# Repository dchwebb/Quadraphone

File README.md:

# Quadraphone

Quadraphone
--------

Quadraphone is a four voice polyphonic analog Voltage Controlled Oscillator for use within a Eurorack Modular Synthesiser. Polyphonic signal interconnections are made via RJ-45 cables (ie Ethernet cables).

Quadraphone features a switchable output of square, triangle and saw waves. Pulse Width Modulation (PWM) is available for the square wave, polyphonically via an RJ-45 input or across all voices via a 3.5mm jack. A potentiometer sets the default pulse width across all voices.

Polyphonic synch is available and a switch allows selection of hard, soft or off settings. Exponentional FM is available on an Rj-45 connection and vibrato (linear FM) is available via a 3.5mm jack with potentiometer attenuation.

A volt per octave input is available on an RJ-45 connector. Pins 1-4 carry the control voltage input and pins 5-8 carry the output signal (also available on an RJ-45) for easy module interconnection. Coarse and Fine tune potentiometers affect all voices.

Technical
---------

Each Quadraphone voice is based around the [Sound Semiconductor SSI2131 Fatkeys VCO](https://www.soundsemiconductor.com/).

Each VCO outputs three voices (pulse, triangle and saw) which are switched via Nexperia 74LV4066PW analog switches. 74LV4066PW ICs are also used to switch incoming synch signals between the hard, soft and off selections.

Each voice has trimmers to control base frequency, exponential scaling and high frequency tracking.

Construction is a sandwich of three PCBs with a component board, a controls board and a panel. PCBs designed in Kicad v6.

[Components schematic](https://raw.githubusercontent.com/dchwebb/Quadraphone/master/Quadraphone_Components.pdf)

[Controls schematic](https://raw.githubusercontent.com/dchwebb/Quadraphone/master/Quadraphone_Controls.pdf)

In addition the the Eurorack +/-12V rails (which have polarity protection and filtering) a 5v rail is supplied using an AMS1117-5.0 LDO. A 2.5v rail is generated with an LM4040DBZ-2.5 and buffered with an MCP6002 opamp and a -5v reference is generated with an LM4040DBZ-5.0.

+12V current draw: 44mA
-12V current draw: 34mA

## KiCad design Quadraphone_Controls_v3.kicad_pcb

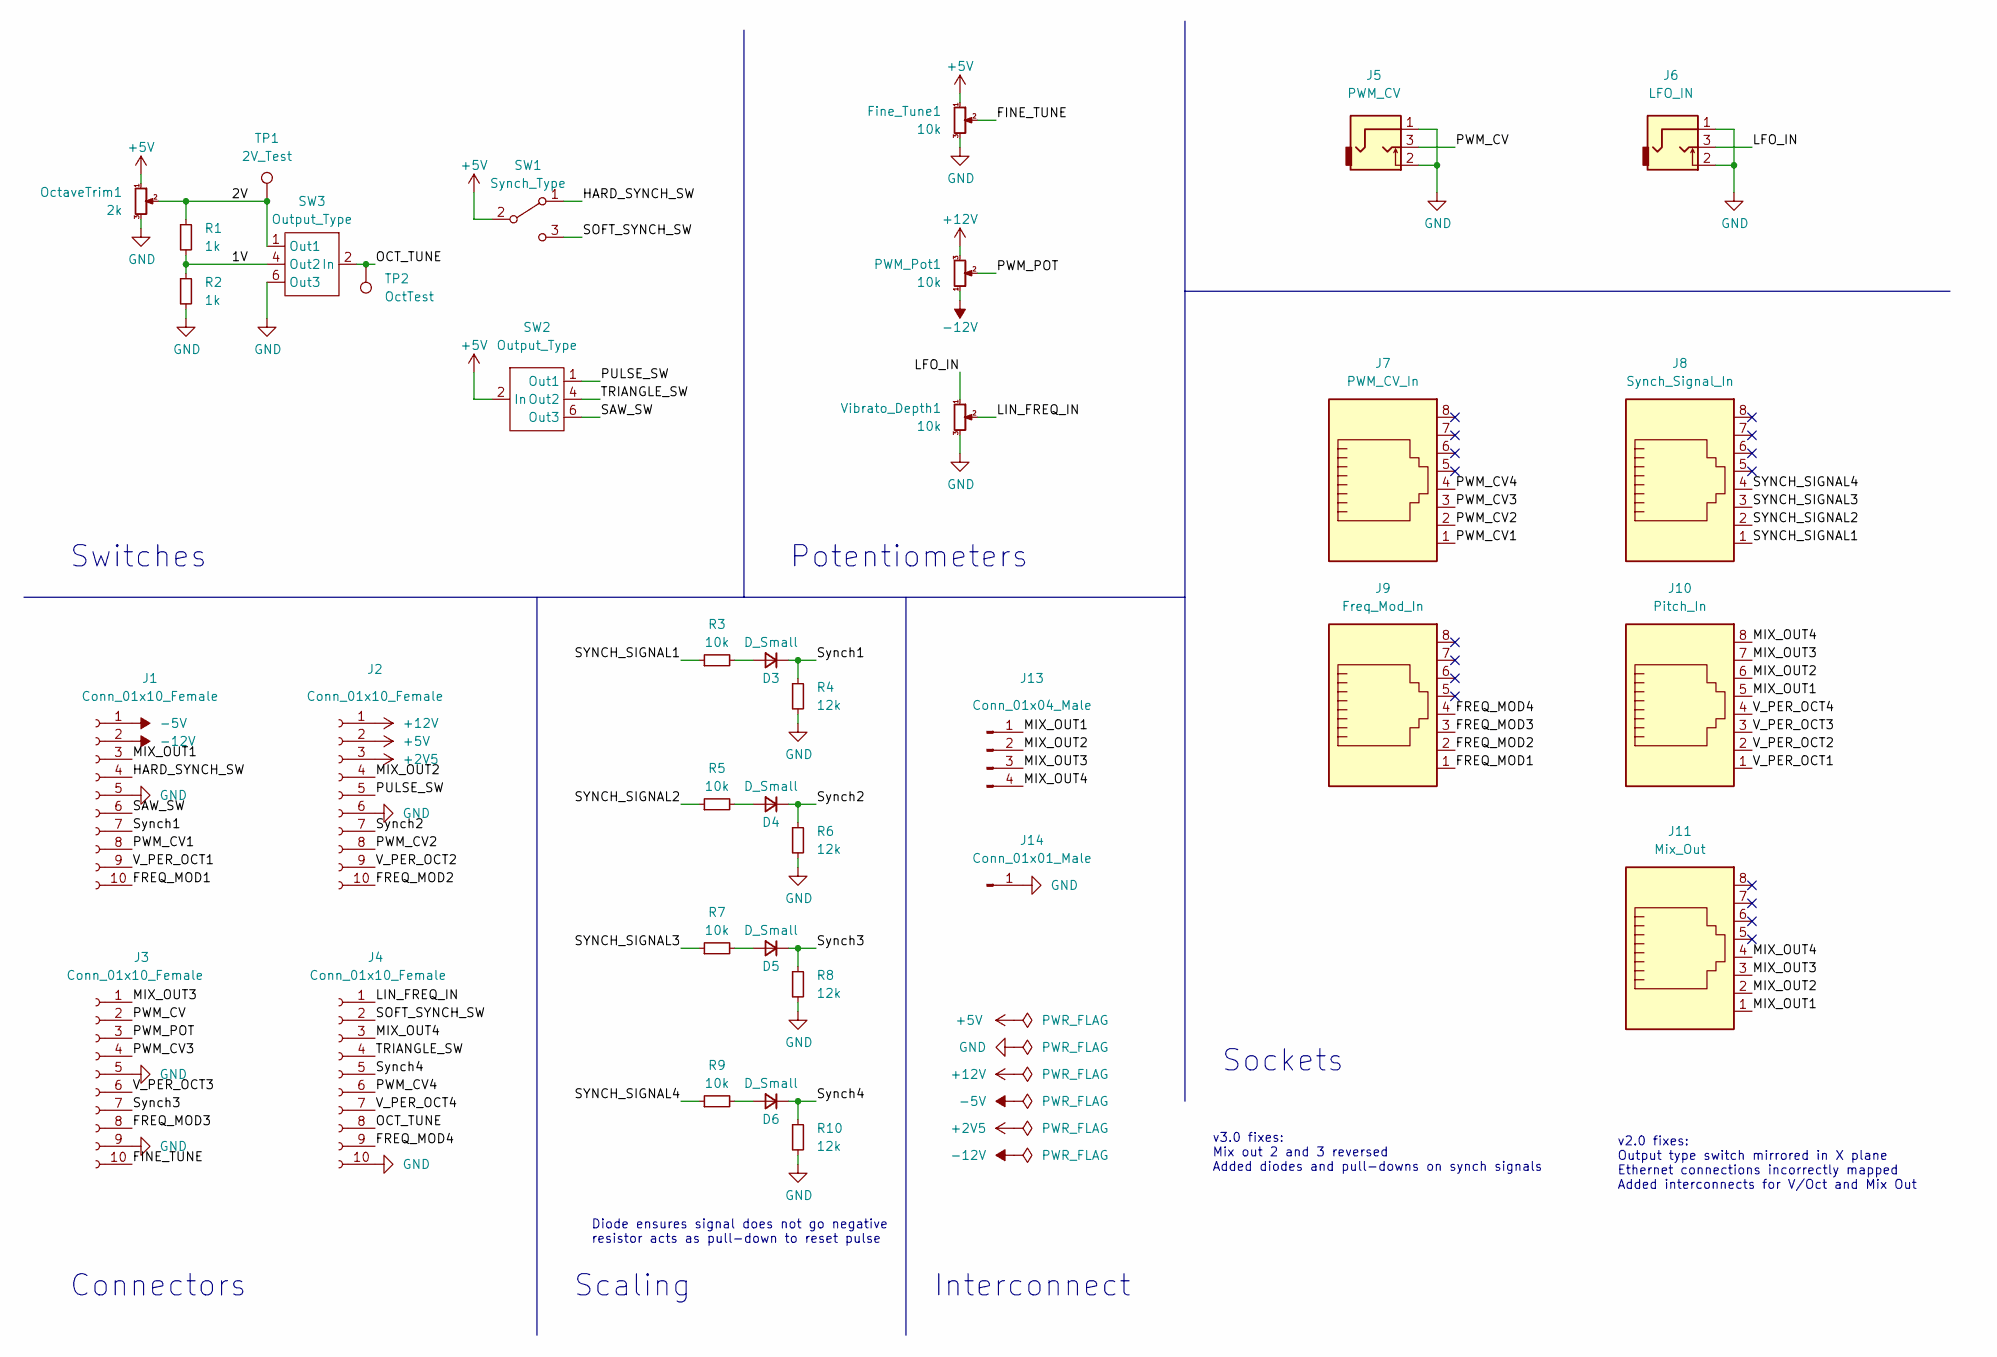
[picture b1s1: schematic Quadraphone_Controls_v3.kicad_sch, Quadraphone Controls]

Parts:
D3, D4, D5, D6: D_Small; D_0603_1608Metric_Pad1.05x0.95mm_HandSolder
Fine_Tune1: 10k; Alpha_9mm_Potentiometer_Aligned
J1, J2, J3, J4: Conn_01x10_Female; PinSocket_1x10_P2.54mm_Vertical
J5: PWM_CV; THONKICONN_hole
J6: LFO_IN; THONKICONN_hole
J7: PWM_CV_In; RJ45_Molex_42878-8506
J8: Synch_Signal_In; RJ45_Molex_42878-8506
J9: Freq_Mod_In; RJ45_Molex_42878-8506
J10: Pitch_In; RJ45_Molex_42878-8506
J11: Mix_Out; RJ45_Molex_42878-8506
J13: Conn_01x04_Male; PinHeader_1x04_P2.54mm_Vertical
J14: Conn_01x01_Male; PinHeader_1x01_P2.54mm_Vertical
OctaveTrim1: 2k; Potentiometer_Bourns_3266W_Vertical
PWM_Pot1: 10k; Alpha_9mm_Potentiometer_Aligned
R1, R2: 1k; R_0805_2012Metric
R3, R5, R7, R9: 10k; R_0805_2012Metric
R4, R6, R8, R10: 12k; R_0805_2012Metric
SW1: Synch_Type; SPDTSubMiniature
SW2, SW3: Output_Type; 100DP6T1B1M2QE_ON_ON_ON
TP1: 2V_Test; 1mm_Test_Point
TP2: OctTest; 1mm_Test_Point
Vibrato_Depth1: 10k; Alpha_9mm_Potentiometer_Aligned

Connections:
+2V5: J2.3
+5V: Fine_Tune1.1, J2.2, OctaveTrim1.1, SW1.2 (B), SW2.2 (In)
+12V: J2.1, PWM_Pot1.3
-5V: J1.1
-12V: J1.2, PWM_Pot1.1
/1V: R1.2, R2.1, SW3.4 (Out2)
/2V: OctaveTrim1.2, R1.1, SW3.1 (Out1), TP1.1
/FINE_TUNE: Fine_Tune1.2, J3.10
/FREQ_MOD1: J1.10, J9.1
/FREQ_MOD2: J2.10, J9.2
/FREQ_MOD3: J3.8, J9.3
/FREQ_MOD4: J4.9, J9.4
/HARD_SYNCH_SW: J1.4, SW1.1 (A)
/LFO_IN: J6.3, Vibrato_Depth1.1
/LIN_FREQ_IN: J4.1, Vibrato_Depth1.2
/MIX_OUT1: J1.3, J10.5, J11.1, J13.1
/MIX_OUT2: J2.4, J10.6, J11.2, J13.2
/MIX_OUT3: J3.1, J10.7, J11.3, J13.3
/MIX_OUT4: J4.3, J10.8, J11.4, J13.4
/OCT_TUNE: J4.8, SW3.2 (In), TP2.1
/PULSE_SW: J2.5, SW2.1 (Out1)
/PWM_CV: J3.2, J5.3
/PWM_CV1: J1.8, J7.1
/PWM_CV2: J2.8, J7.2
/PWM_CV3: J3.4, J7.3
/PWM_CV4: J4.6, J7.4
/PWM_POT: J3.3, PWM_Pot1.2
/SAW_SW: J1.6, SW2.6 (Out3)
/SOFT_SYNCH_SW: J4.2, SW1.3 (C)
/SYNCH_SIGNAL1: J8.1, R3.1
/SYNCH_SIGNAL2: J8.2, R5.1
/SYNCH_SIGNAL3: J8.3, R7.1
/SYNCH_SIGNAL4: J8.4, R9.1
/Synch1: D3.1 (K), J1.7, R4.1
/Synch2: D4.1 (K), J2.7, R6.1
/Synch3: D5.1 (K), J3.7, R8.1
/Synch4: D6.1 (K), J4.5, R10.1
/TRIANGLE_SW: J4.4, SW2.4 (Out2)
/V_PER_OCT1: J1.9, J10.1
/V_PER_OCT2: J2.9, J10.2
/V_PER_OCT3: J3.6, J10.3
/V_PER_OCT4: J4.7, J10.4
GND: Fine_Tune1.3, J1.5, J2.6, J3.5, J3.9, J4.10, J5.1, J5.2, J6.1, J6.2, J14.1, OctaveTrim1.3, R2.2, R4.2, R6.2, R8.2, R10.2, SW3.6 (Out3), Vibrato_Depth1.3
unnamed: D3.2 (A), R3.2
unnamed: D4.2 (A), R5.2
unnamed: D5.2 (A), R7.2
unnamed: D6.2 (A), R9.2
unnamed: SW2.3 (Pin3), SW2.5 (Pin5)
unnamed: SW3.3 (Pin3), SW3.5 (Pin5)

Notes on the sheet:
Connectors
Diode ensures signal does not go negative resistor acts as pull-down to reset pulse
Scaling
Potentiometers
v2.0 fixes: Output type switch mirrored in X plane Ethernet connections incorrectly mapped Added interconnects for V/Oct and Mix Out
v3.0 fixes: Mix out 2 and 3 reversed Added diodes and pull-downs on synch signals
Sockets
Switches
Interconnect

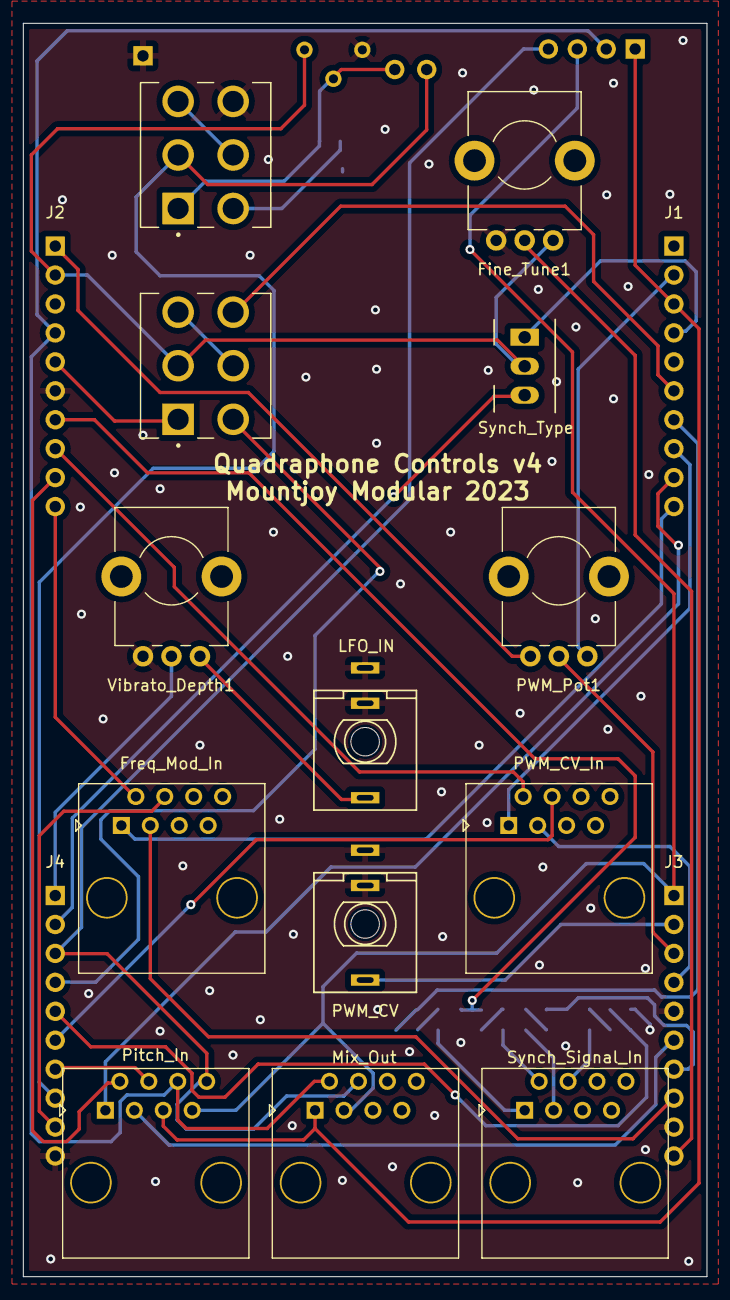
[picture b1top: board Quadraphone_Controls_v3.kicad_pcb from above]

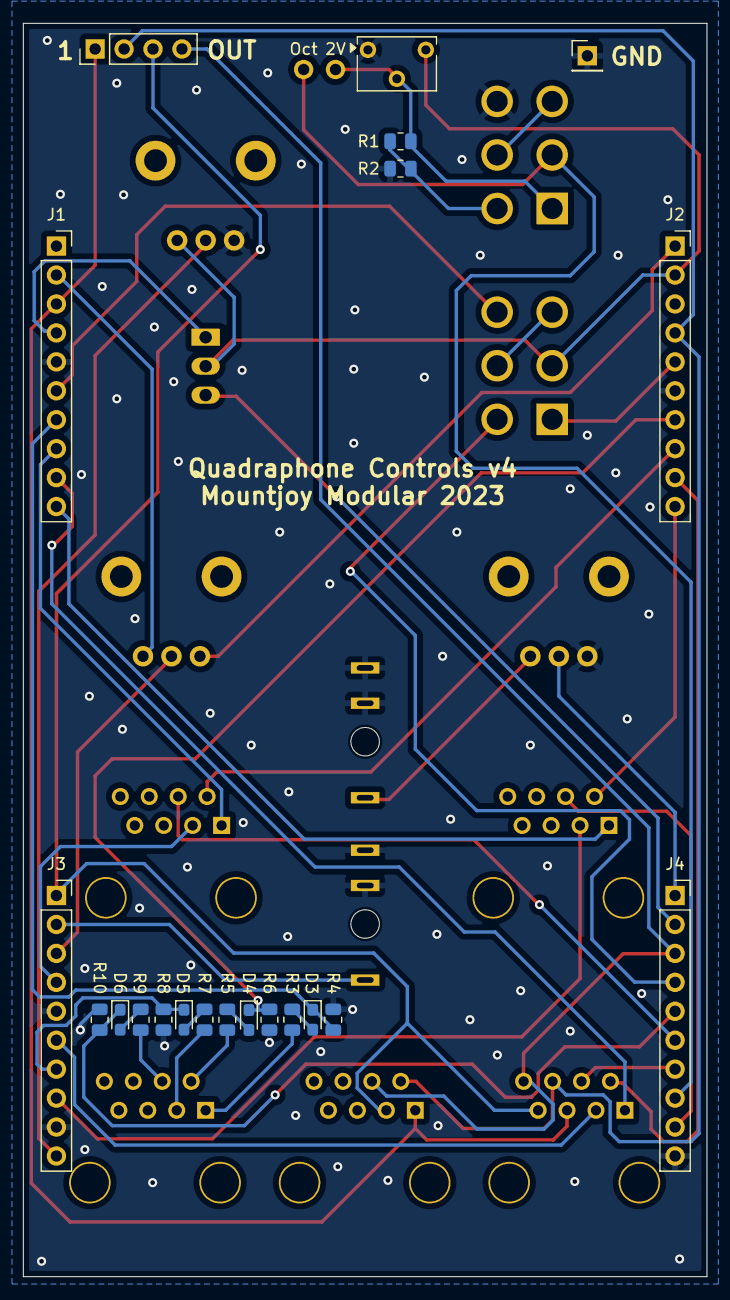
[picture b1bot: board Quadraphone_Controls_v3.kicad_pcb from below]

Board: 2 copper layers, 60.0 x 110.0 mm, 36 parts (21 on the bottom side), 47 nets.

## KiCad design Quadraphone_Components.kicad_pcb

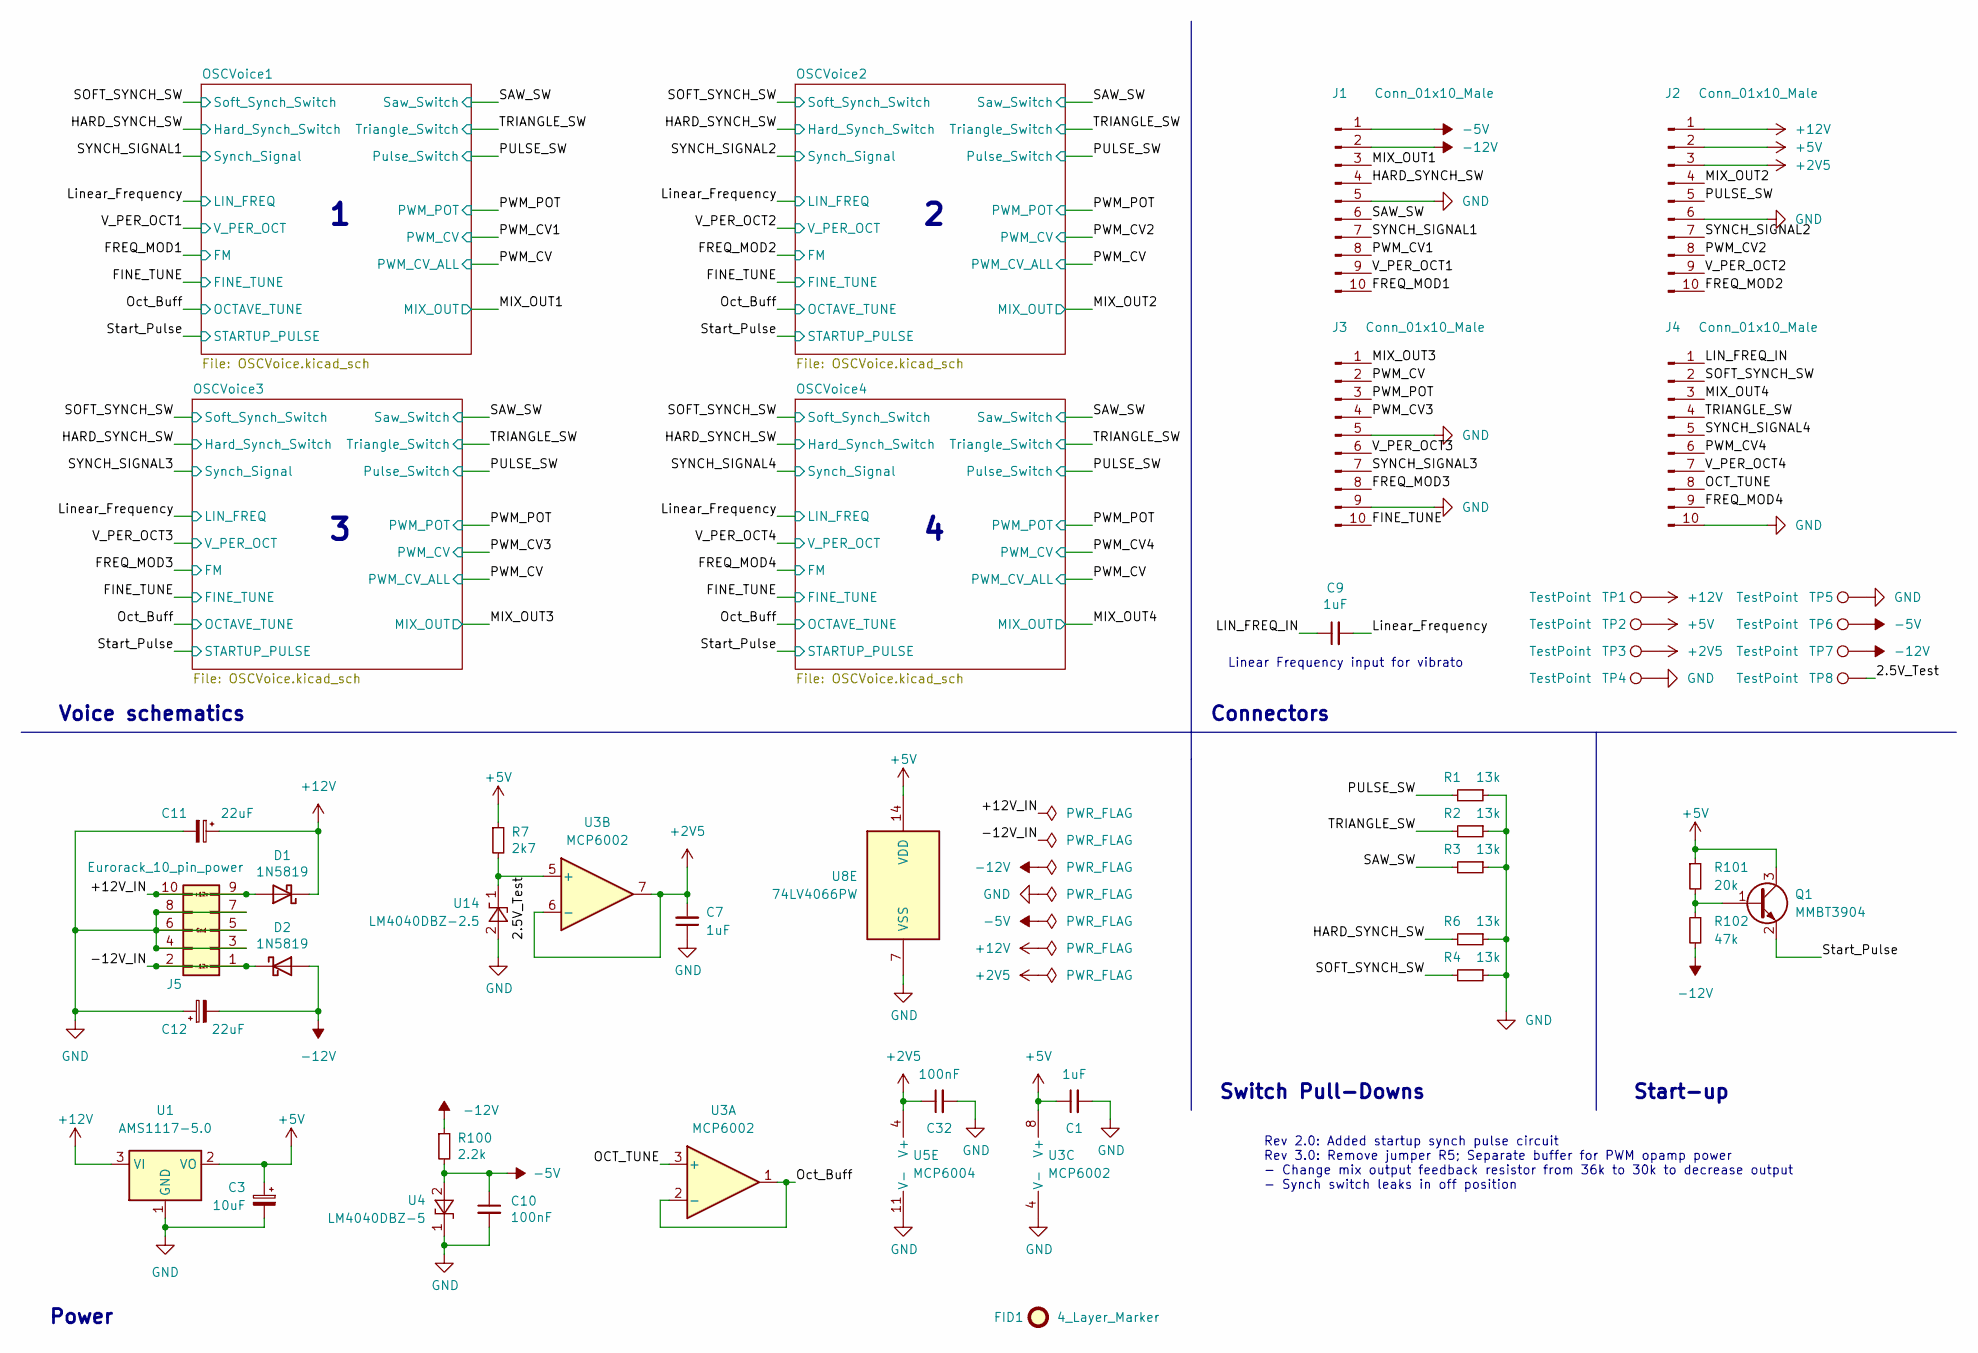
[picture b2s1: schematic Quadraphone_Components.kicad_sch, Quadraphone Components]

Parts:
C1, C7, C9: 1uF; C_0603_1608Metric_Pad1.08x0.95mm_HandSolder
C3: 10uF; CP_Elec_4x5.7
C10, C32: 100nF; C_0603_1608Metric_Pad1.08x0.95mm_HandSolder
C11, C12: 22uF; CP_Elec_4x5.8
D1, D2: 1N5819; D_SOD-123
FID1: 4_Layer_Marker; 4_Layer_Markers
J1, J2, J3, J4: Conn_01x10_Male; PinHeader_1x10_P2.54mm_Vertical
J5: Eurorack_10_pin_power; Eurorack_10_pin_header
Q1: MMBT3904; SOT-23
R1, R2, R3, R4, R6: 13k; R_0603_1608Metric
R7: 2k7; R_0603_1608Metric
R100: 2.2k; R_0603_1608Metric
R101: 20k; R_0603_1608Metric
R102: 47k; R_0603_1608Metric
TP1, TP2, TP3, TP4, TP5, TP6, TP7, TP8: TestPoint; 1.3mm_Test_Point
U1: AMS1117-5.0; SOT-223-3_TabPin2
U3: MCP6002; SOIC-8_3.9x4.9mm_P1.27mm
U4: LM4040DBZ-5; SOT-23
U5: MCP6004; SOIC-14_3.9x8.7mm_P1.27mm
U8: 74LV4066PW; TSSOP-14_4.4x5mm_P0.65mm
U14: LM4040DBZ-2.5; SOT-23

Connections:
+2V5: C7.2, C32.1, J2.3, TP3.1, U3.6 (-), U3.7, U5.4 (V+); also elsewhere on the board
+5V: C1.1, C3.1, J2.2, Q1.3 (C), R7.1, R101.1, TP2.1, U1.2 (VO), U3.8 (V+), U8.14 (VDD); also elsewhere on the board
+12V: C11.1, D1.1 (K), J2.1, TP1.1, U1.3 (VI); also elsewhere on the board
-5V: C10.1, J1.1, R100.2, TP6.1, U4.2 (A); also elsewhere on the board
-12V: C12.2, D2.2 (A), J1.2, R100.1, R102.2, TP7.1; also elsewhere on the board
/2.5V_Test: R7.2, TP8.1, U3.5 (+), U14.1 (K)
/+12V_IN: D1.2 (A), J5.9, J5.10
/-12V_IN: D2.1 (K), J5.1, J5.2
/FINE_TUNE: J3.10; also elsewhere on the board
/FREQ_MOD1: J1.10; also elsewhere on the board
/FREQ_MOD2: J2.10; also elsewhere on the board
/FREQ_MOD3: J3.8; also elsewhere on the board
/FREQ_MOD4: J4.9; also elsewhere on the board
/HARD_SYNCH_SW: J1.4, R6.2; also elsewhere on the board
/LIN_FREQ_IN: C9.1, J4.1
/Linear_Frequency: C9.2; also elsewhere on the board
/MIX_OUT1: J1.3; also elsewhere on the board
/MIX_OUT2: J2.4; also elsewhere on the board
/MIX_OUT3: J3.1; also elsewhere on the board
/MIX_OUT4: J4.3; also elsewhere on the board
/OCT_TUNE: J4.8, U3.3 (+)
/OSCVoice1/PWM_Control: U5.7; also elsewhere on the board
/OSCVoice1/PWM_Opamp_Mix: U5.6 (-); also elsewhere on the board
/OSCVoice1/Soft_Synch: U8.9; also elsewhere on the board
/OSCVoice2/PWM_Control: U5.1; also elsewhere on the board
/OSCVoice2/PWM_Opamp_Mix: U5.2 (-); also elsewhere on the board
/OSCVoice2/Soft_Synch: U8.3; also elsewhere on the board
/OSCVoice4/PWM_Control: U5.14; also elsewhere on the board
/OSCVoice4/PWM_Opamp_Mix: U5.13 (-); also elsewhere on the board
/OSCVoice4/Soft_Synch: U8.2; also elsewhere on the board
/Oct_Buff: U3.1, U3.2 (-); also elsewhere on the board
/PULSE_SW: J2.5, R1.2; also elsewhere on the board
/PWM_CV: J3.2; also elsewhere on the board
/PWM_CV1: J1.8; also elsewhere on the board
/PWM_CV2: J2.8; also elsewhere on the board
/PWM_CV3: J3.4; also elsewhere on the board
/PWM_CV4: J4.6; also elsewhere on the board
/PWM_POT: J3.3; also elsewhere on the board
/SAW_SW: J1.6, R3.2; also elsewhere on the board
/SOFT_SYNCH_SW: J4.2, R4.2, U8.5, U8.6, U8.13; also elsewhere on the board
/SYNCH_SIGNAL1: J1.7, U8.8; also elsewhere on the board
/SYNCH_SIGNAL2: J2.7, U8.4; also elsewhere on the board
/SYNCH_SIGNAL3: J3.7; also elsewhere on the board
/SYNCH_SIGNAL4: J4.5, U8.1; also elsewhere on the board
/Start_Pulse: Q1.2 (E); also elsewhere on the board
/TRIANGLE_SW: J4.4, R2.2; also elsewhere on the board
/V_PER_OCT1: J1.9; also elsewhere on the board
/V_PER_OCT2: J2.9; also elsewhere on the board
/V_PER_OCT3: J3.6; also elsewhere on the board
/V_PER_OCT4: J4.7; also elsewhere on the board
GND: C1.2, C3.2, C7.1, C10.2, C11.2, C12.1, C32.2, J1.5, J2.6, J3.5, J3.9, J4.10, J5.3, J5.4, J5.5, J5.6, J5.7, J5.8, R1.1, R2.1, R3.1, R4.1, R6.1, TP4.1, TP5.1, U1.1 (GND), U3.4 (V-), U4.1 (K), U5.3 (+), U5.5 (+), U5.11 (V-), U5.12 (+), U8.7 (VSS), U14.2 (A); also elsewhere on the board
unnamed: Q1.1 (B), R101.2, R102.1

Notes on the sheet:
Rev 2.0: Added startup synch pulse circuit Rev 3.0: Remove jumper R5; Separate buffer for PWM opamp power - Change mix output feedback resistor from 36k to 30k to decrease output - Synch switch leaks in off position
Linear Frequency input for vibrato
Start-up
Switch Pull-Downs
Connectors
Power
Voice schematics

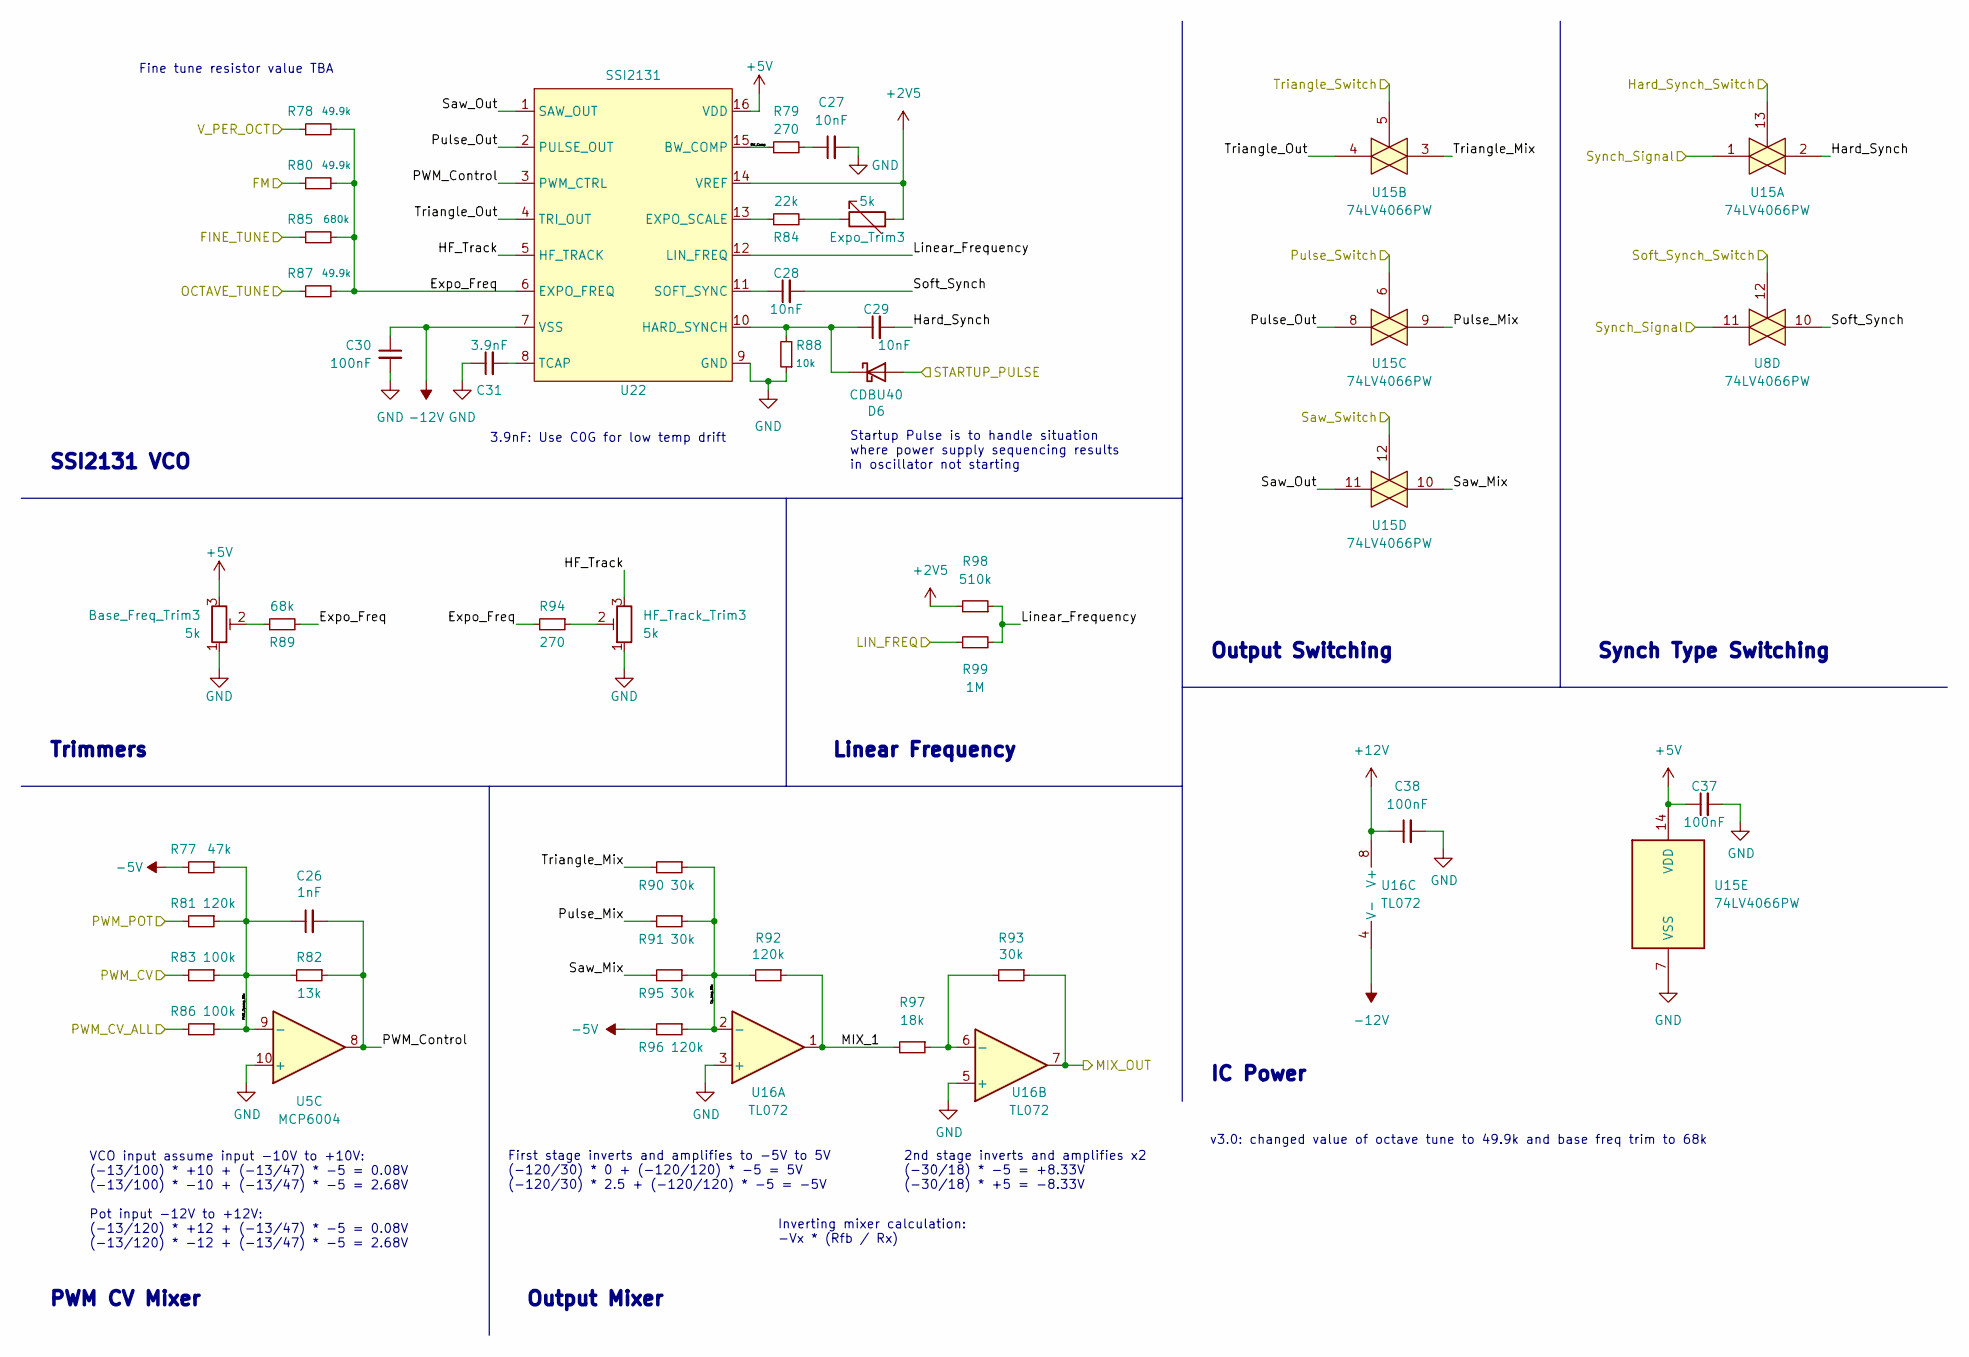
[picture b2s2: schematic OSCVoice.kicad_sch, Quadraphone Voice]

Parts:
Base_Freq_Trim3: 5k; Potentiometer_Bourns_3266W_Vertical
C26: 1nF; C_0603_1608Metric_Pad1.08x0.95mm_HandSolder
C27, C28, C29: 10nF; C_0603_1608Metric_Pad1.08x0.95mm_HandSolder
C30, C37, C38: 100nF; C_0603_1608Metric_Pad1.08x0.95mm_HandSolder
C31: 3.9nF; C_0603_1608Metric_Pad1.08x0.95mm_HandSolder
D6: CDBU40; D_0603_1608Metric
Expo_Trim3: 5k; Potentiometer_Bourns_3266W_Vertical
HF_Track_Trim3: 5k; Potentiometer_Bourns_3266W_Vertical
R77: 47k; R_0603_1608Metric
R78, R80, R87: 49.9k; R_0603_1608Metric
R79, R94: 270; R_0603_1608Metric
R81, R92, R96: 120k; R_0603_1608Metric
R82: 13k; R_0603_1608Metric
R83, R86: 100k; R_0603_1608Metric
R84: 22k; R_0603_1608Metric
R85: 680k; R_0603_1608Metric
R88: 10k; R_0603_1608Metric
R89: 68k; R_0603_1608Metric
R90, R91, R93, R95: 30k; R_0603_1608Metric
R97: 18k; R_0603_1608Metric
R98: 510k; R_0603_1608Metric
R99: 1M; R_0603_1608Metric
U5: MCP6004; SOIC-14_3.9x8.7mm_P1.27mm
U8, U15: 74LV4066PW; TSSOP-14_4.4x5mm_P0.65mm
U16: TL072; SOIC-8_3.9x4.9mm_P1.27mm
U22: SSI2131; SOIC-16_3.9x9.9mm_P1.27mm

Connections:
+2V5: Expo_Trim3.2, R98.2, U22.14 (VREF); also elsewhere on the board
+5V: Base_Freq_Trim3.3, C37.1, U15.14 (VDD), U22.16 (VDD); also elsewhere on the board
+12V: C38.1, U16.8 (V+); also elsewhere on the board
-5V: R77.2, R96.2; also elsewhere on the board
-12V: C30.1, U16.4 (V-), U22.7 (VSS); also elsewhere on the board
/FINE_TUNE: R85.1; also elsewhere on the board
/FREQ_MOD3: R80.1; also elsewhere on the board
/HARD_SYNCH_SW: U15.13; also elsewhere on the board
/Linear_Frequency: R99.1; also elsewhere on the board
/MIX_OUT3: R93.1, U16.7; also elsewhere on the board
/OSCVoice1/PWM_Control: U5.7; also elsewhere on the board
/OSCVoice1/PWM_Opamp_Mix: U5.6 (-); also elsewhere on the board
/OSCVoice1/Soft_Synch: U8.9; also elsewhere on the board
/OSCVoice2/PWM_Control: U5.1; also elsewhere on the board
/OSCVoice2/PWM_Opamp_Mix: U5.2 (-); also elsewhere on the board
/OSCVoice2/Soft_Synch: U8.3; also elsewhere on the board
/OSCVoice3/BW_Comp: R79.1, U22.15 (BW_COMP)
/OSCVoice3/Expo_Freq: R78.2, R80.2, R85.2, R87.2, R89.2, R94.2, U22.6 (EXPO_FREQ)
/OSCVoice3/HF_Track: HF_Track_Trim3.3, U22.5 (HF_TRACK)
/OSCVoice3/Hard_Synch: C29.2, U15.2
/OSCVoice3/Linear_Frequency: R98.1, R99.2, U22.12 (LIN_FREQ)
/OSCVoice3/MIX_1: R92.1, R97.2, U16.1
/OSCVoice3/Op_Amp_Mix: R90.1, R91.1, R92.2, R95.1, R96.1, U16.2 (-)
/OSCVoice3/PWM_Control: C26.2, R82.1, U5.8, U22.3 (PWM_CTRL)
/OSCVoice3/PWM_Opamp_Mix: C26.1, R77.1, R81.1, R82.2, R83.1, R86.1, U5.9 (-)
/OSCVoice3/Pulse_Mix: R91.2, U15.9
/OSCVoice3/Pulse_Out: U15.8, U22.2 (PULSE_OUT)
/OSCVoice3/Saw_Mix: R95.2, U15.10
/OSCVoice3/Saw_Out: U15.11, U22.1 (SAW_OUT)
/OSCVoice3/Soft_Synch: C28.2, U8.10
/OSCVoice3/Triangle_Mix: R90.2, U15.3
/OSCVoice3/Triangle_Out: U15.4, U22.4 (TRI_OUT)
/OSCVoice4/PWM_Control: U5.14; also elsewhere on the board
/OSCVoice4/PWM_Opamp_Mix: U5.13 (-); also elsewhere on the board
/OSCVoice4/Soft_Synch: U8.2; also elsewhere on the board
/Oct_Buff: R87.1; also elsewhere on the board
/PULSE_SW: U15.6; also elsewhere on the board
/PWM_CV: R86.2; also elsewhere on the board
/PWM_CV3: R83.2; also elsewhere on the board
/PWM_POT: R81.2; also elsewhere on the board
/SAW_SW: U15.12; also elsewhere on the board
/SOFT_SYNCH_SW: U8.5, U8.6, U8.12, U8.13; also elsewhere on the board
/SYNCH_SIGNAL1: U8.8; also elsewhere on the board
/SYNCH_SIGNAL2: U8.4; also elsewhere on the board
/SYNCH_SIGNAL3: U8.11, U15.1; also elsewhere on the board
/SYNCH_SIGNAL4: U8.1; also elsewhere on the board
/Start_Pulse: D6.2 (A); also elsewhere on the board
/TRIANGLE_SW: U15.5; also elsewhere on the board
/V_PER_OCT3: R78.1; also elsewhere on the board
GND: Base_Freq_Trim3.1, C27.2, C30.2, C31.1, C37.2, C38.2, HF_Track_Trim3.1, R88.1, U5.3 (+), U5.5 (+), U5.10 (+), U5.12 (+), U15.7 (VSS), U16.3 (+), U16.5 (+), U22.9 (GND); also elsewhere on the board
unnamed: Base_Freq_Trim3.2, R89.1
unnamed: C27.1, R79.2
unnamed: C29.1, D6.1 (K), R88.2, U22.10 (HARD_SYNCH)
unnamed: Expo_Trim3.1, R84.2
unnamed: HF_Track_Trim3.2, R94.1
unnamed: R93.2, R97.1, U16.6 (-)
unnamed: R84.1, U22.13 (EXPO_SCALE)
unnamed: C28.1, U22.11 (SOFT_SYNC)
unnamed: C31.2, U22.8 (TCAP)

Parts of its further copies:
Base_Freq_Trim1, Base_Freq_Trim2, Base_Freq_Trim4: 5k; Potentiometer_Bourns_3266W_Vertical
C4, C5, C6, C15, C16, C17, C21, C22, C23: 10nF; C_0603_1608Metric_Pad1.08x0.95mm_HandSolder
C8, C19, C25: 3.9nF; C_0603_1608Metric_Pad1.08x0.95mm_HandSolder
C13, C14, C20: 1nF; C_0603_1608Metric_Pad1.08x0.95mm_HandSolder
C18, C24, C33, C34, C35, C36, C39, C40, C41: 100nF; C_0603_1608Metric_Pad1.08x0.95mm_HandSolder
D3, D4, D5: CDBU40; D_0603_1608Metric
Expo_Trim1, Expo_Trim2, Expo_Trim4: 5k; Potentiometer_Bourns_3266W_Vertical
HF_Track_Trim1, HF_Track_Trim2, HF_Track_Trim4: 5k; Potentiometer_Bourns_3266W_Vertical
R8, R38, R61: 22k; R_0603_1608Metric
R9, R42, R65: 10k; R_0603_1608Metric
R10, R16, R33, R48, R56, R71: 270; R_0603_1608Metric
R11, R31, R54: 47k; R_0603_1608Metric
R12, R21, R28, R35, R46, R50, R58, R69, R73: 120k; R_0603_1608Metric
R13, R15, R25, R40, R60, R63: 100k; R_0603_1608Metric
R14, R36, R59: 13k; R_0603_1608Metric
R17, R39, R62: 680k; R_0603_1608Metric
R18, R22, R32, R34, R37, R41, R55, R57, R64: 49.9k; R_0603_1608Metric
R19, R20, R26, R27, R44, R45, R47, R49, R67, R68, R70, R72: 30k; R_0603_1608Metric
R23, R43, R66: 68k; R_0603_1608Metric
R24, R52, R75: 510k; R_0603_1608Metric
R29, R51, R74: 18k; R_0603_1608Metric
R30, R53, R76: 1M; R_0603_1608Metric
U6, U7, U11: 74LV4066PW; TSSOP-14_4.4x5mm_P0.65mm
U9, U12, U17: SSI2131; SOIC-16_3.9x9.9mm_P1.27mm
U10, U13, U18: TL072; SOIC-8_3.9x4.9mm_P1.27mm

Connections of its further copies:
+2V5: Expo_Trim1.2, Expo_Trim2.2, Expo_Trim4.2, R24.2, R52.2, R75.2, U9.14 (VREF), U12.14 (VREF), U17.14 (VREF); also elsewhere on the board
+5V: Base_Freq_Trim1.3, Base_Freq_Trim2.3, Base_Freq_Trim4.3, C33.1, C35.1, C39.1, U6.14 (VDD), U7.14 (VDD), U9.16 (VDD), U11.14 (VDD), U12.16 (VDD), U17.16 (VDD); also elsewhere on the board
+12V: C34.1, C36.1, C40.1, U10.8 (V+), U13.8 (V+), U18.8 (V+); also elsewhere on the board
-5V: R11.2, R28.2, R31.2, R50.2, R54.2, R73.2; also elsewhere on the board
-12V: C18.1, C24.1, C41.1, U9.7 (VSS), U10.4 (V-), U12.7 (VSS), U13.4 (V-), U17.7 (VSS), U18.4 (V-); also elsewhere on the board
/FINE_TUNE: R17.1, R39.1, R62.1; also elsewhere on the board
/FREQ_MOD1: R18.1; also elsewhere on the board
/FREQ_MOD2: R34.1; also elsewhere on the board
/FREQ_MOD4: R57.1; also elsewhere on the board
/HARD_SYNCH_SW: U6.13, U7.13, U11.13; also elsewhere on the board
/Linear_Frequency: R30.1, R53.1, R76.1; also elsewhere on the board
/MIX_OUT1: R26.1, U10.7; also elsewhere on the board
/MIX_OUT2: R47.1, U13.7; also elsewhere on the board
/MIX_OUT4: R70.1, U18.7; also elsewhere on the board
/OSCVoice1/BW_Comp: R10.1, U9.15 (BW_COMP)
/OSCVoice1/Expo_Freq: R16.2, R17.2, R18.2, R22.2, R23.2, R37.2, U9.6 (EXPO_FREQ)
/OSCVoice1/HF_Track: HF_Track_Trim1.3, U9.5 (HF_TRACK)
/OSCVoice1/Hard_Synch: C6.2, U6.2
/OSCVoice1/Linear_Frequency: R24.1, R30.2, U9.12 (LIN_FREQ)
/OSCVoice1/MIX_1: R21.1, R29.2, U10.1
/OSCVoice1/Op_Amp_Mix: R19.1, R20.1, R21.2, R27.1, R28.1, U10.2 (-)
/OSCVoice1/PWM_Control: C13.2, R14.1, U9.3 (PWM_CTRL); also elsewhere on the board
/OSCVoice1/PWM_Opamp_Mix: C13.1, R11.1, R12.1, R14.2, R15.1, R25.1; also elsewhere on the board
/OSCVoice1/Pulse_Mix: R20.2, U6.9
/OSCVoice1/Pulse_Out: U6.8, U9.2 (PULSE_OUT)
/OSCVoice1/Saw_Mix: R27.2, U6.10
/OSCVoice1/Saw_Out: U6.11, U9.1 (SAW_OUT)
/OSCVoice1/Soft_Synch: C5.2; also elsewhere on the board
/OSCVoice1/Triangle_Mix: R19.2, U6.3
/OSCVoice1/Triangle_Out: U6.4, U9.4 (TRI_OUT)
/OSCVoice2/BW_Comp: R33.1, U12.15 (BW_COMP)
/OSCVoice2/Expo_Freq: R32.2, R34.2, R39.2, R41.2, R43.2, R48.2, U12.6 (EXPO_FREQ)
/OSCVoice2/HF_Track: HF_Track_Trim2.3, U12.5 (HF_TRACK)
/OSCVoice2/Hard_Synch: C17.2, U7.2
/OSCVoice2/Linear_Frequency: R52.1, R53.2, U12.12 (LIN_FREQ)
/OSCVoice2/MIX_1: R46.1, R51.2, U13.1
/OSCVoice2/Op_Amp_Mix: R44.1, R45.1, R46.2, R49.1, R50.1, U13.2 (-)
/OSCVoice2/PWM_Control: C14.2, R36.1, U12.3 (PWM_CTRL); also elsewhere on the board
/OSCVoice2/PWM_Opamp_Mix: C14.1, R31.1, R35.1, R36.2, R40.1, R60.1; also elsewhere on the board
/OSCVoice2/Pulse_Mix: R45.2, U7.9
/OSCVoice2/Pulse_Out: U7.8, U12.2 (PULSE_OUT)
/OSCVoice2/Saw_Mix: R49.2, U7.10
/OSCVoice2/Saw_Out: U7.11, U12.1 (SAW_OUT)
/OSCVoice2/Soft_Synch: C16.2; also elsewhere on the board
/OSCVoice2/Triangle_Mix: R44.2, U7.3
/OSCVoice2/Triangle_Out: U7.4, U12.4 (TRI_OUT)
/OSCVoice4/BW_Comp: R56.1, U17.15 (BW_COMP)
/OSCVoice4/Expo_Freq: R55.2, R57.2, R62.2, R64.2, R66.2, R71.2, U17.6 (EXPO_FREQ)
/OSCVoice4/HF_Track: HF_Track_Trim4.3, U17.5 (HF_TRACK)
/OSCVoice4/Hard_Synch: C23.2, U11.2
/OSCVoice4/Linear_Frequency: R75.1, R76.2, U17.12 (LIN_FREQ)
/OSCVoice4/MIX_1: R69.1, R74.2, U18.1
/OSCVoice4/Op_Amp_Mix: R67.1, R68.1, R69.2, R72.1, R73.1, U18.2 (-)
/OSCVoice4/PWM_Control: C20.2, R59.1, U17.3 (PWM_CTRL); also elsewhere on the board
/OSCVoice4/PWM_Opamp_Mix: C20.1, R13.1, R54.1, R58.1, R59.2, R63.1; also elsewhere on the board
/OSCVoice4/Pulse_Mix: R68.2, U11.9
/OSCVoice4/Pulse_Out: U11.8, U17.2 (PULSE_OUT)
/OSCVoice4/Saw_Mix: R72.2, U11.10
/OSCVoice4/Saw_Out: U11.11, U17.1 (SAW_OUT)
/OSCVoice4/Soft_Synch: C22.2; also elsewhere on the board
/OSCVoice4/Triangle_Mix: R67.2, U11.3
/OSCVoice4/Triangle_Out: U11.4, U17.4 (TRI_OUT)
/Oct_Buff: R22.1, R41.1, R64.1; also elsewhere on the board
/PULSE_SW: U6.6, U7.6, U11.6; also elsewhere on the board
/PWM_CV: R15.2, R40.2, R63.2; also elsewhere on the board
/PWM_CV1: R25.2; also elsewhere on the board
/PWM_CV2: R60.2; also elsewhere on the board
/PWM_CV4: R13.2; also elsewhere on the board
/PWM_POT: R12.2, R35.2, R58.2; also elsewhere on the board
/SAW_SW: U6.12, U7.12, U11.12; also elsewhere on the board
/SYNCH_SIGNAL1: U6.1; also elsewhere on the board
/SYNCH_SIGNAL2: U7.1; also elsewhere on the board
/SYNCH_SIGNAL4: U11.1; also elsewhere on the board
/Start_Pulse: D3.2 (A), D4.2 (A), D5.2 (A); also elsewhere on the board
/TRIANGLE_SW: U6.5, U7.5, U11.5; also elsewhere on the board
/V_PER_OCT1: R37.1; also elsewhere on the board
/V_PER_OCT2: R32.1; also elsewhere on the board
/V_PER_OCT4: R55.1; also elsewhere on the board
GND: Base_Freq_Trim1.1, Base_Freq_Trim2.1, Base_Freq_Trim4.1, C4.2, C8.1, C15.2, C18.2, C19.1, C21.2, C24.2, C25.1, C33.2, C34.2, C35.2, C36.2, C39.2, C40.2, C41.2, HF_Track_Trim1.1, HF_Track_Trim2.1, HF_Track_Trim4.1, R9.1, R42.1, R65.1, U6.7 (VSS), U7.7 (VSS), U9.9 (GND), U10.3 (+), U10.5 (+), U11.7 (VSS), U12.9 (GND), U13.3 (+), U13.5 (+), U17.9 (GND), U18.3 (+), U18.5 (+); also elsewhere on the board
unnamed: Base_Freq_Trim1.2, R23.1
unnamed: Base_Freq_Trim2.2, R43.1
unnamed: Base_Freq_Trim4.2, R66.1
unnamed: C4.1, R10.2
unnamed: C15.1, R33.2
unnamed: C21.1, R56.2
unnamed: C6.1, D3.1 (K), R9.2, U9.10 (HARD_SYNCH)
unnamed: C17.1, D4.1 (K), R42.2, U12.10 (HARD_SYNCH)
unnamed: C23.1, D5.1 (K), R65.2, U17.10 (HARD_SYNCH)
unnamed: Expo_Trim1.1, R8.2
unnamed: Expo_Trim2.1, R38.2
unnamed: Expo_Trim4.1, R61.2
unnamed: HF_Track_Trim1.2, R16.1
unnamed: HF_Track_Trim2.2, R48.1
unnamed: HF_Track_Trim4.2, R71.1
unnamed: R8.1, U9.13 (EXPO_SCALE)
unnamed: C5.1, U9.11 (SOFT_SYNC)
unnamed: C8.2, U9.8 (TCAP)
unnamed: R26.2, R29.1, U10.6 (-)
unnamed: R38.1, U12.13 (EXPO_SCALE)
unnamed: C16.1, U12.11 (SOFT_SYNC)
unnamed: C19.2, U12.8 (TCAP)
unnamed: R47.2, R51.1, U13.6 (-)
unnamed: R61.1, U17.13 (EXPO_SCALE)
unnamed: C22.1, U17.11 (SOFT_SYNC)
unnamed: C25.2, U17.8 (TCAP)
unnamed: R70.2, R74.1, U18.6 (-)

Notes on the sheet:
First stage inverts and amplifies to -5V to 5V (-120/30) * 0 + (-120/120) * -5 = 5V (-120/30) * 2.5 + (-120/120) * -5 = -5V
Startup Pulse is to handle situation where power supply sequencing results in oscillator not starting
Fine tune resistor value TBA
PWM CV Mixer
Synch Type Switching
Inverting mixer calculation: -Vx * (Rfb / Rx)
SSI2131 VCO
Linear Frequency
VCO input assume input -10V to +10V: (-13/100) * +10 + (-13/47) * -5 = 0.08V (-13/100) * -10 + (-13/47) * -5 = 2.68V Pot input -12V to +12V: (-13/120) * +12 + (-13/47) * -5 = 0.08V (-13/120) * -12 + (-13/47) * -5 = 2.68V
Trimmers
Output Mixer
v3.0: changed value of octave tune to 49.9k and base freq trim to 68k
3.9nF: Use C0G for low temp drift
IC Power
2nd stage inverts and amplifies x2 (-30/18) * -5 = +8.33V (-30/18) * +5 = -8.33V
Output Switching
